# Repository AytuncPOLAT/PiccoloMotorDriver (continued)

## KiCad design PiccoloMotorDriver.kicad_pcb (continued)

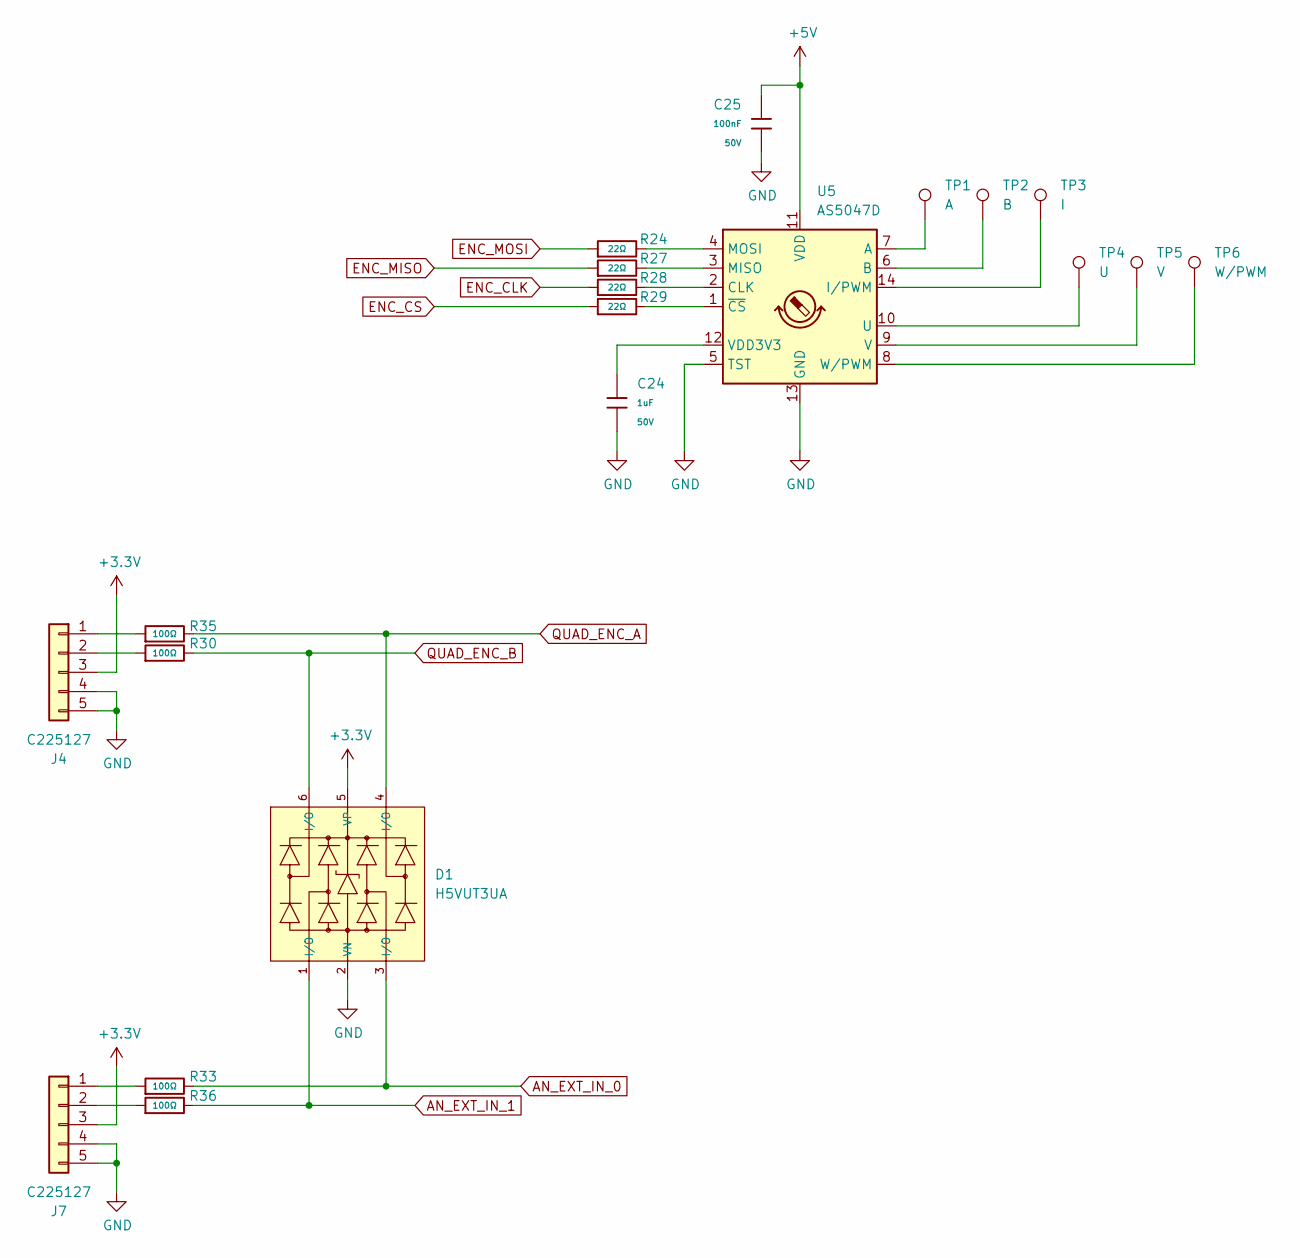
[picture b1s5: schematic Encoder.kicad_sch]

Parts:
C24: 1uF; C_0603; Voltage Rated 50V; Tolerance ±10%; Part CL10A105KB8NNNC; LCSC C15849
C25: 100nF; C_0603; Voltage Rated 50V; Tolerance ±10%; Part CC0603KRX7R9BB104; LCSC C14663
D1: H5VUT3UA; SOT-363_L2.1-W1.3-P0.65-LS2.2-BL; Part H5VUT3UA; LCSC C20615830
J4, J7: C225127; JST_GH_SM04B-GHS-TB_1x04-1MP_P1.25mm_Horizontal; LCSC C225127
R24, R27, R28, R29: 22Ω; R_0603; Overload Voltage (Max) 75V; Tolerance ±1%; Part 0603WAF220JT5E; LCSC C23345
R30, R33, R35, R36: 100Ω; R_0603; Overload Voltage (Max) 75V; Tolerance ±1%; Part 0603WAF1000T5E; LCSC C22775
TP1: A; TestPoint_Pad_D1.0mm
TP2: B; TestPoint_Pad_D1.0mm
TP3: I; TestPoint_Pad_D1.0mm
TP4: U; TestPoint_Pad_D1.0mm
TP5: V; TestPoint_Pad_D1.0mm
TP6: W/PWM; TestPoint_Pad_D1.0mm
U5: AS5047D; TSSOP-14_4.4x5mm_P0.65mm; LCSC C55112284

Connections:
+3.3V: D1.5 (VP), J4.3, J7.3; also elsewhere on the board
+5V: C25.1, U5.11 (VDD); also elsewhere on the board
AN_EXT_IN_0: D1.3 (I/O), R33.2; also elsewhere on the board
AN_EXT_IN_1: D1.1 (I/O), R36.2; also elsewhere on the board
ENC_CLK: R28.1; also elsewhere on the board
ENC_CS: R29.1; also elsewhere on the board
ENC_MISO: R27.1; also elsewhere on the board
ENC_MOSI: R24.1; also elsewhere on the board
GND: C24.2, C25.2, D1.2 (VN), J4.4, J4.5, J7.4, J7.5, U5.5 (TST), U5.13 (GND); also elsewhere on the board
unnamed: J4.1, R35.1
unnamed: J4.2, R30.1
unnamed: J7.1, R33.1
unnamed: J7.2, R36.1
unnamed: TP1.1 (1_1), U5.7 (A)
unnamed: TP2.1 (1_1), U5.6 (B)
unnamed: R28.2, U5.2 (CLK)
unnamed: TP3.1 (1_1), U5.14 (I/PWM)
unnamed: R27.2, U5.3 (MISO)
unnamed: R24.2, U5.4 (MOSI)
unnamed: TP4.1 (1_1), U5.10 (U)
unnamed: TP5.1 (1_1), U5.9 (V)
unnamed: C24.1, U5.12 (VDD3V3)
unnamed: TP6.1 (1_1), U5.8 (W/PWM)
unnamed: R29.2, U5.1 (~CS)
QUAD_ENC_A: D1.4 (I/O), R35.2; also elsewhere on the board
QUAD_ENC_B: D1.6 (I/O), R30.2; also elsewhere on the board

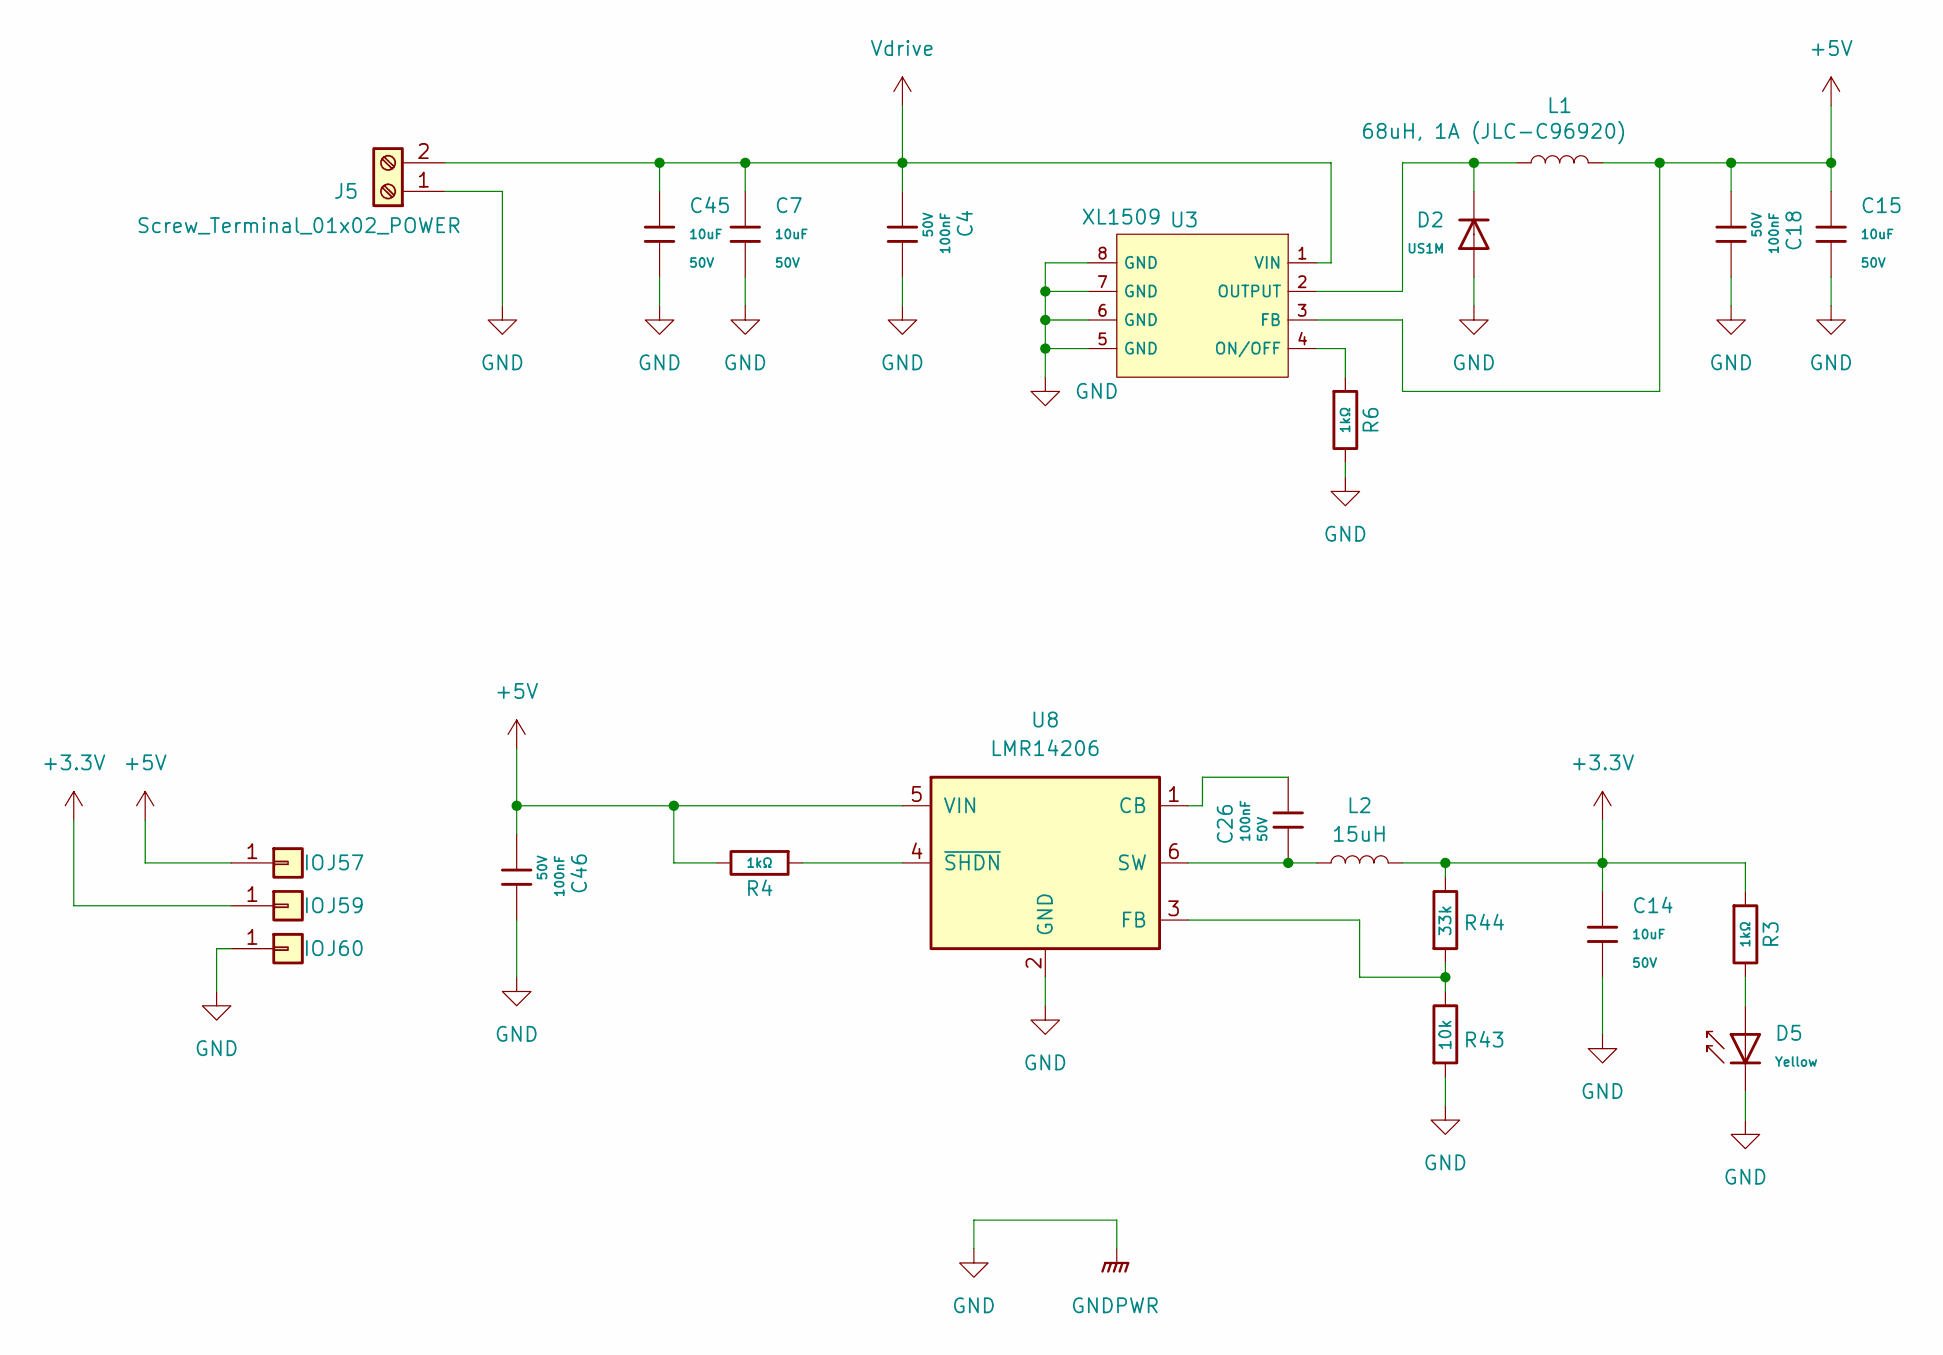
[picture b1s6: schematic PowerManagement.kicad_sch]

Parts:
C4, C18, C26, C46: 100nF; C_0603; Voltage Rated 50V; Tolerance ±10%; Part CC0603KRX7R9BB104; LCSC C14663
C7, C14, C15, C45: 10uF; C_1206; Voltage Rated 50V; Tolerance ±10%; Part CL31A106KBHNNNE; LCSC C13585
D2: US1M; D_SMA; Forward Voltage (Vf@If) 1.65V@1A; Reverse Voltage (Vr) 1kV; Part US1M; LCSC C412437
D5: Yellow; D_0603; Forward Voltage (VF) 1.6V~2.6V; Part NCD0603Y2; LCSC C89811
J5: Screw_Terminal_01x02_POWER; AMASS_XT30PW-M_1x02_P2.50mm_Horizontal; LCSC C431092
J57, J59, J60: IO; TestPoint_THTPad_D1.0mm_Drill0.5mm
L1: 68uH, 1A (JLC-C96920); L_Changjiang_FNR5020S; LCSC C96920
L2: 15uH; L_Changjiang_FNR3021S; LCSC C257180
R3, R4, R6: 1kΩ; R_0603; Overload Voltage (Max) 75V; Tolerance ±1%; Part 0603WAF1001T5E; LCSC C21190
R43: 10k; R_0603
R44: 33k; R_0603
U3: XL1509; SOIC-8_L5.0-W4.0-P1.27-LS6.0-BL; Output Voltage 5V; Input Voltage 4.5V~40V; Part XL1509-5.0E1; LCSC C61063
U8: LMR14206; SOT-23-6

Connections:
+3.3V: C14.1, J59.1 (Pin_1_1), L2.2, R3.1, R44.1; also elsewhere on the board
+5V: C15.1, C18.1, C46.1, J57.1 (Pin_1_1), L1.2, R4.2, U3.3 (FB), U8.5 (VIN); also elsewhere on the board
GND: C4.2, C7.2, C14.2, C15.2, C18.2, C45.2, C46.2, D2.2, D5.1, J5.1, J60.1 (Pin_1_1), R6.2, R43.2, U3.5 (GND), U3.6 (GND), U3.7 (GND), U3.8 (GND), U8.2 (GND); also elsewhere on the board
unnamed: D5.2, R3.2
unnamed: R6.1, U3.4 (ON/OFF)
unnamed: D2.1, L1.1, U3.2 (OUTPUT)
unnamed: C26.2, U8.1 (CB)
unnamed: R43.1, R44.2, U8.3 (FB)
unnamed: C26.1, L2.1, U8.6 (SW)
unnamed: R4.1, U8.4 (~SHDN)
Vdrive: C4.1, C7.1, C45.1, J5.2, U3.1 (VIN); also elsewhere on the board

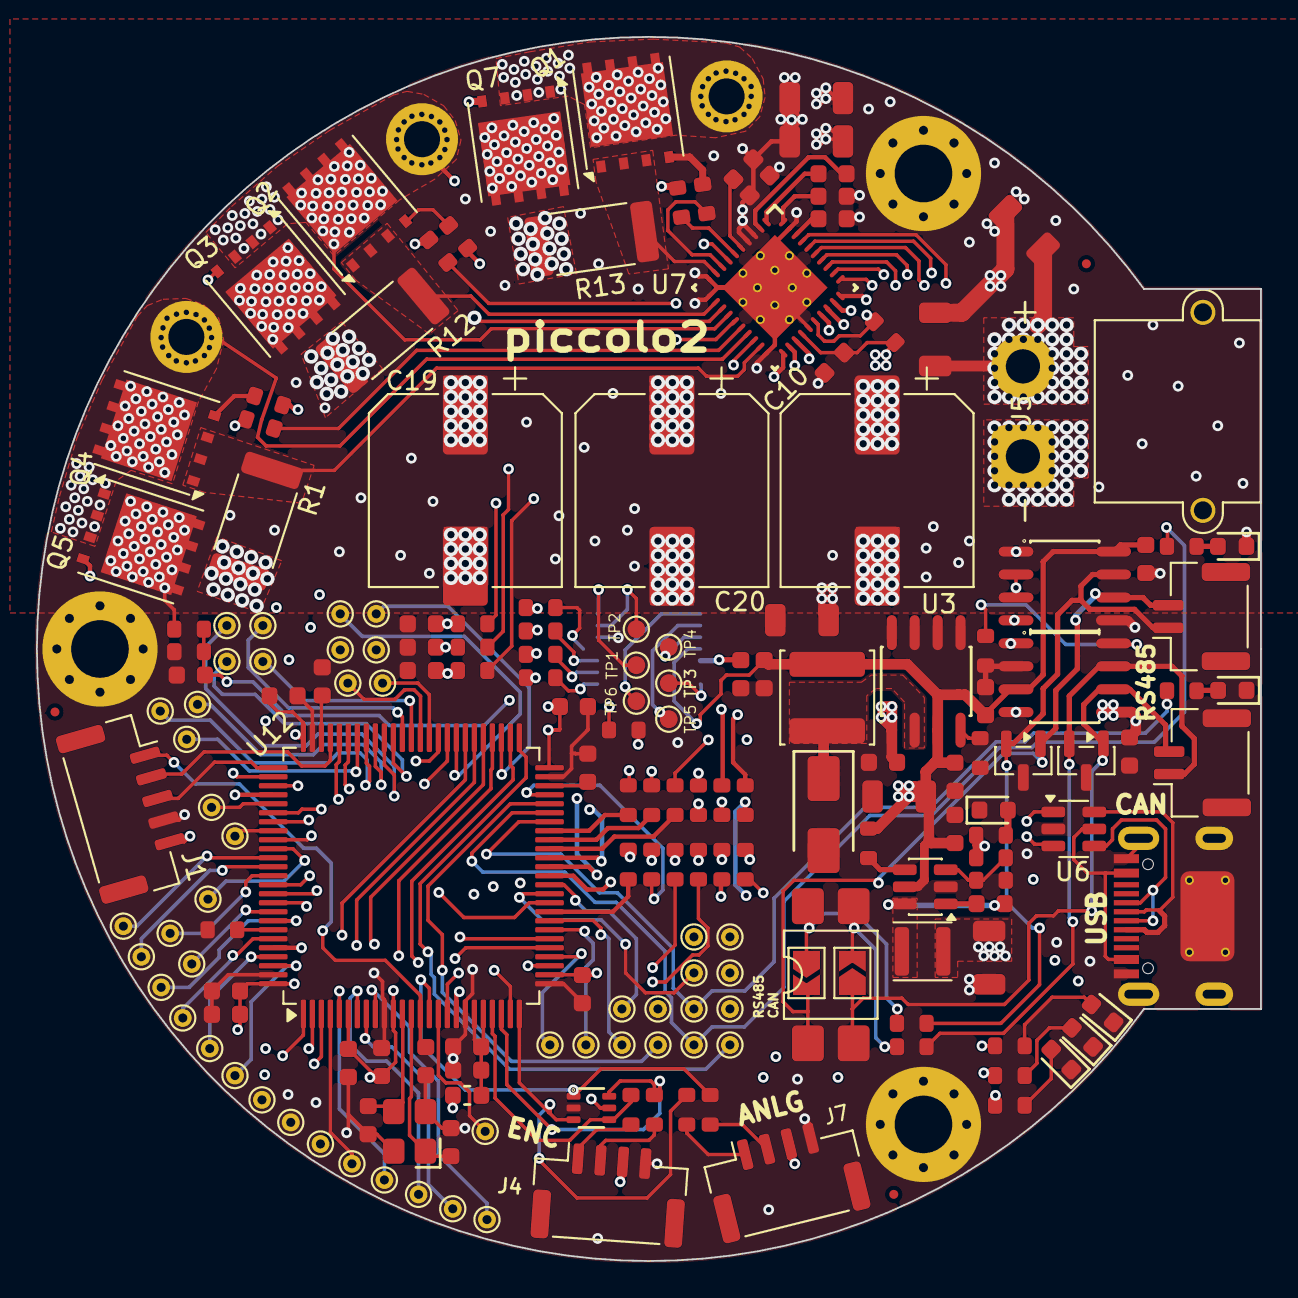
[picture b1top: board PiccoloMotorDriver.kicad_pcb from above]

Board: 6 copper layers, 68.0 x 68.0 mm, 193 parts (1 on the bottom side), 166 nets.

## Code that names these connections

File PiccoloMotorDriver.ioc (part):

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Mcu.Name=STM32H723VGHx
Mcu.Package=TFBGA100
Mcu.UserName=STM32H723VGHx
PA13(JTMS/SWDIO).Mode=Serial_Wire
PA13(JTMS/SWDIO).Signal=DEBUG_JTMS-SWDIO
PA14(JTCK/SWCLK).Mode=Serial_Wire
PA14(JTCK/SWCLK).Signal=DEBUG_JTCK-SWCLK
PA2.Signal=ADCx_INP14
PA3.Signal=ADCx_INP15
PA8.Mode=Clock-out-1
PA8.Signal=RCC_MCO_1
PC0.Signal=ADCx_INP10
PC1.Signal=ADCx_INP11
PD0.Mode=FDCAN_Activate
PD0.Signal=FDCAN1_RX
PD1.Mode=FDCAN_Activate
PD1.Signal=FDCAN1_TX
PE11.Signal=S_TIM1_CH2
PE12.Signal=TIM1_CH3N
PE13.Signal=S_TIM1_CH3
PH0-OSC_IN.Mode=HSE-External-Oscillator
PH0-OSC_IN.Signal=RCC_OSC_IN
PH1-OSC_OUT.Mode=HSE-External-Oscillator
PH1-OSC_OUT.Signal=RCC_OSC_OUT
RCC.SYSCLKFreq_VALUE=64000000
board=custom

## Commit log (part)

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2025-07-07 Add IO sub schematic, add communications
2025-07-19 add IO, MCU, power sheets
2025-07-21 Add encoder sheet
2025-08-04 Add buck converter, add part of pinmap to mcu
2025-08-25 Add mcu connections
2025-09-12 Added DRV layout
2025-10-03 Re arrange connectors
2025-10-06 updated mcu connections
2025-10-09 layout placement
2025-10-13 more layout
2025-11-01 Reroute mcu lines, updated can, motor timer pins
2025-12-07 Finished layout, pcba is being tested
2026-01-21 Added render image
2026-03-23 updated read-me
2026-03-23 Add MIT License to the project
